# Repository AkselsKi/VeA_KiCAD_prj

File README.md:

# VeA_KiCAD_prj
Paredzets kursa projektiem

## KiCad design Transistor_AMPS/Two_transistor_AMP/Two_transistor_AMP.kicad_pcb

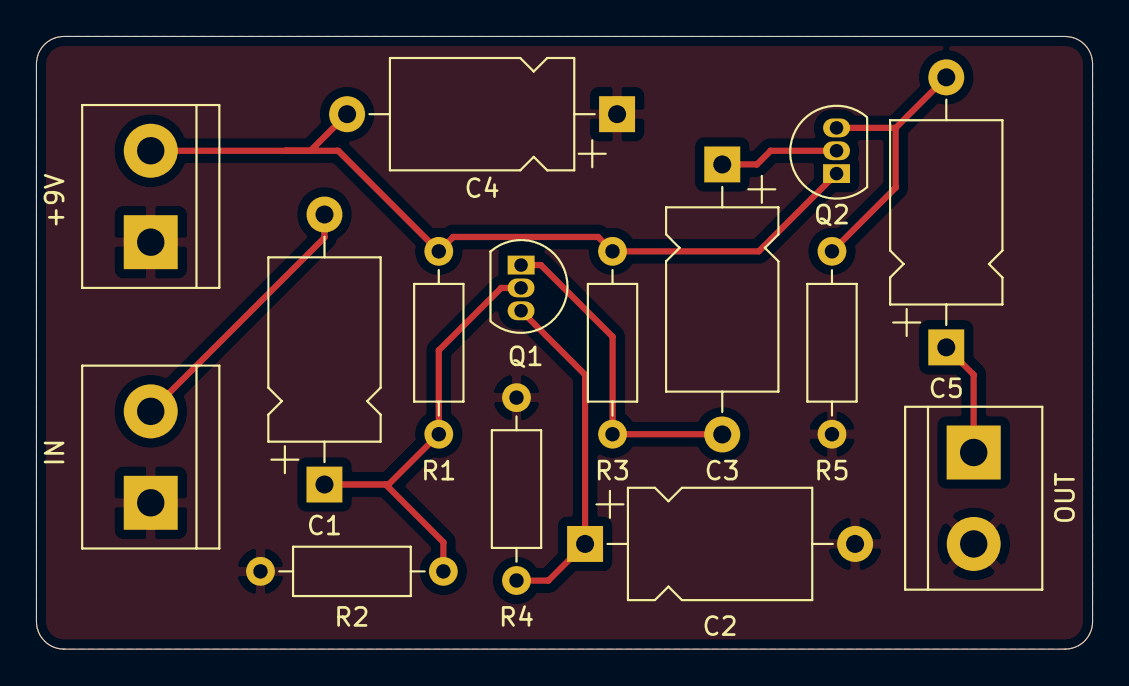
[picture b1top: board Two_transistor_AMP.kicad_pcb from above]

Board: 2 copper layers, 58.7 x 34.0 mm, 15 parts (0 on the bottom side), 9 nets.

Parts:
+9V: Screw_Terminal_01x02; TerminalBlock_bornier-2_P5.08mm
C1, C3: 0.47u; CP_Axial_L10.0mm_D6.0mm_P15.00mm_Horizontal
C2: 4.7u; CP_Axial_L10.0mm_D6.0mm_P15.00mm_Horizontal
C4: 47u; CP_Axial_L10.0mm_D6.0mm_P15.00mm_Horizontal
C5: 33u; CP_Axial_L10.0mm_D6.0mm_P15.00mm_Horizontal
IN: Screw_Terminal_01x02; TerminalBlock_bornier-2_P5.08mm
OUT: Screw_Terminal_01x02; TerminalBlock_bornier-2_P5.08mm
Q1, Q2: BC546; TO-92L_Inline
R1: 220k; R_Axial_DIN0207_L6.3mm_D2.5mm_P10.16mm_Horizontal
R2: 27k; R_Axial_DIN0207_L6.3mm_D2.5mm_P10.16mm_Horizontal
R3, R5: 10k; R_Axial_DIN0207_L6.3mm_D2.5mm_P10.16mm_Horizontal
R4: 1k5; R_Axial_DIN0207_L6.3mm_D2.5mm_P10.16mm_Horizontal

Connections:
+9V: +9V.2, C4.2, Q2.1, R1.1, R3.1
GNDREF: +9V.1, C2.2, C4.1, IN.1, OUT.2, R2.2, R4.2, R5.2
unnamed: C1.1, Q1.2, R1.2, R2.1
unnamed: C1.2, IN.2
unnamed: C2.1, Q1.3, R4.1
unnamed: C3.1, Q2.2
unnamed: C3.2, Q1.1, R3.2
unnamed: C5.1, OUT.1
unnamed: C5.2, Q2.3, R5.1

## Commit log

2021-09-29 README update to test GitHub Repo
2021-10-04 A_Kirsons_MultiVib update to test GitHub Repo
2021-10-21 PWR_Supply update to test GitHub Repo
2021-11-01 Majasdarbs update to test GitHub Repo
2021-11-27 Majasdarbs update
2021-12-06 majasdarbs
